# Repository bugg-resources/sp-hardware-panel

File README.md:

# sp-hardware-panel

This repository contains the KiCad source files for the panelled version of the PCBs required for the Bugg recording device (``main``, ``led``, and ``mic``). 

Also hosted here is the itemised BoM for the whole project.

For a full overview of the design of the Bugg recording device and practical assembly instructions please refer to the [Bugg hardware handover document](https://raw.githubusercontent.com/bugg-resources/bugg-handover/master/bugg-handover.pdf?token=GHSAT0AAAAAABSRG7B7T6BEZWMJQBPE7FNYYSNI6KQ).

## Electronics overview

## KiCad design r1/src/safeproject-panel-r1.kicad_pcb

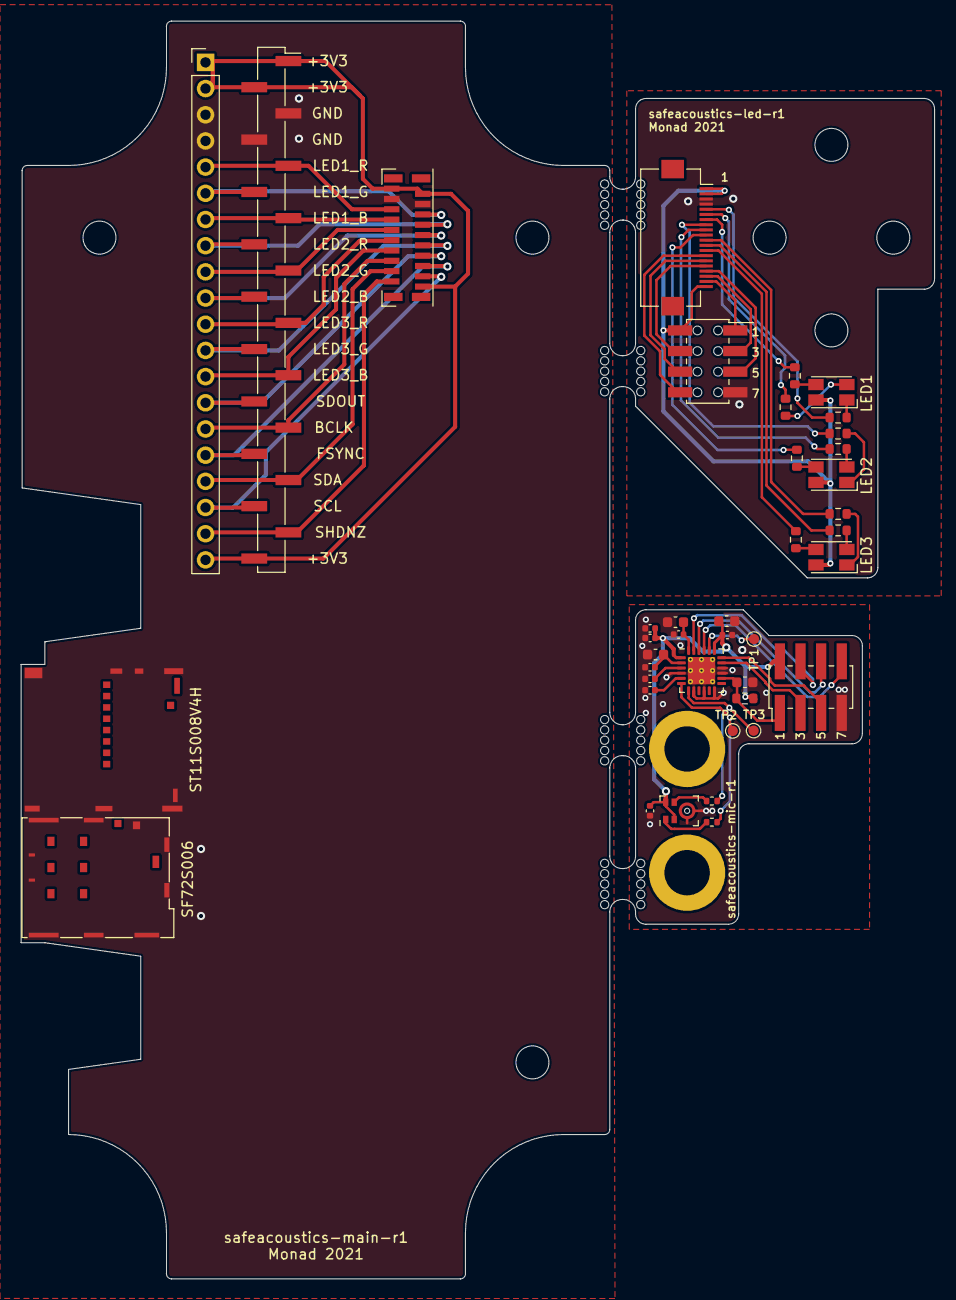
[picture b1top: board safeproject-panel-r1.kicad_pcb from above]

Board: 2 copper layers, 88.6 x 122.0 mm, 40 parts (0 on the bottom side), 37 nets.

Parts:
C1, C5, C7, C9, C11: 100nF; C_0402_1005Metric
C2, C3, C6: 1uF; C_0402_1005Metric
C4, C8, C10, C12: 10uF; C_0603_1608Metric
J1: 2842142-4; PinSocket_2x04_P2.00mm_Vertical_SMD_Bottom_or_Top_Entry_AMP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
J1#2: JAE_SIM_Card_SF72S006
J1#3: 2842142-4; PinHeader_2x04_P2.00mm_Vertical_SMD_AMPMODU
J2: Conn_01x20; Hirose_FH12-20S-0.5SH_1x20-1MP_P0.50mm_Horizontal
J2#2: Conn_01x20; Hirose_FH12-20S-0.5SVA_1x20-1MP_P0.50mm_Vertical
J3: Micro_SD_Card_Det_JAE_ST11; microSD_JAE_ST11S008V4H
J4: Conn_01x20; PinHeader_1x20_P2.54mm_Vertical_SMD_Pin1Right
J5: Conn_01x20; PinHeader_1x20_P2.54mm_Vertical
LED1, LED2, LED3: IN-P32TATRGB; LED_Avago_PLCC4_3.2x2.8mm_CW
MK1: SPH0641LU4H-1; Knowles_LGA-5_3.5x2.65mm
R1, R2#2, R3, R4, R5, R6: 22R; R_0603_1608Metric
R1#2, R2: 22R; R_0402_1005Metric
R3#2: 10k; R_0603_1608Metric
R7, R8, R9: 100R; R_0603_1608Metric
TP1, TP2, TP3: TestPoint; TestPoint_Pad_D1.0mm
U1: PCMD3180; QFN-24-1EP_4x4mm_P0.5mm_EP2.65x2.65mm_ThermalVias

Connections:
+3V3: C1.1, C6.2, C7.2, C10.1, C11.1, J1.2, J1#3.2, J2.1, J2.2, J2.20, LED1.2 (A), LED2.2 (A), LED3.2 (A), MK1.2 (SEL), MK1.5 (VDD), R3#2.2, U1.1 (AVDD), U1.19 (IOVDD)
/+3V3: J2#2.1, J2#2.2, J2#2.20, J4.1, J4.2, J4.20, J5.1, J5.2, J5.20
/BCLK: J1.6, J1#3.6, J2.15, J2#2.15, J4.15, J5.15, U1.22 (BCLK)
/FSYNC: J1.4, J1#3.4, J2.16, J2#2.16, J4.16, J5.16, U1.23 (FSYNC)
/GND: J1#2.SH, J2#2.3, J2#2.4, J3.GND, J4.3, J4.4, J5.3, J5.4
/LED1_B: J2.7, J2#2.7, J4.7, J5.7, R1.1
/LED1_G: J2.6, J2#2.6, J4.6, J5.6, R4.1
/LED1_R: J2.5, J2#2.5, J4.5, J5.5, R7.1
/LED2_B: J2.10, J2#2.10, J4.10, J5.10, R2#2.1
/LED2_G: J2.9, J2#2.9, J4.9, J5.9, R5.1
/LED2_R: J2.8, J2#2.8, J4.8, J5.8, R8.1
/LED3_B: J2.13, J2#2.13, J4.13, J5.13, R3.1
/LED3_G: J2.12, J2#2.12, J4.12, J5.12, R6.1
/LED3_R: J2.11, J2#2.11, J4.11, J5.11, R9.1
/SCL: J1.3, J1#3.3, J2.18, J2#2.18, J4.18, J5.18, U1.17 (SCL_MOSI)
/SDA: J1.5, J1#3.5, J2.17, J2#2.17, J4.17, J5.17, U1.18 (SDA_SSZ)
/SDOUT: J1.8, J1#3.8, J2.14, J2#2.14, J4.14, J5.14, U1.21 (SDOUT)
/SHDNZ: C12.2, J1.1, J1#3.1, J2.19, J2#2.19, J4.19, J5.19, R3#2.1, U1.14 (SHDNZ)
GND: C1.2, C2.1, C3.1, C4.1, C5.1, C6.1, C7.1, C8.1, C9.1, C10.2, C11.2, C12.1, J1.7, J1#3.7, J2.3, J2.4, MK1.3 (GND), U1.4 (AVSS), U1.8 (PDMDIN2_GPI2), U1.10 (PDMDIN3_GPI3), U1.12 (PDMDIN4_GPI4), U1.15 (ADDR1_MISO), U1.16 (ADDR0_SCLK), U1.25 (VSS_THERMAL)
unnamed: C2.2, U1.5 (MICBIAS)
unnamed: C3.2, U1.3 (VREF)
unnamed: C4.2, C5.2, U1.2 (AREG)
unnamed: C8.2, C9.2, U1.24 (DREG)
unnamed: LED1.1 (RK), R7.2
unnamed: LED1.3 (BK), R1.2
unnamed: LED1.4 (GK), R4.2
unnamed: LED2.1 (RK), R8.2
unnamed: LED2.3 (BK), R2#2.2
unnamed: LED2.4 (GK), R5.2
unnamed: LED3.1 (RK), R9.2
unnamed: LED3.3 (BK), R3.2
unnamed: LED3.4 (GK), R6.2
unnamed: MK1.1 (DATA), R1#2.1
unnamed: MK1.4 (CLOCK), R2.1
unnamed: R1#2.2, TP2.1, U1.6 (PDMDIN1_GPI1)
unnamed: R2.2, TP3.1, U1.7 (PDMCLK1_GPO1)
unnamed: TP1.1, U1.20 (GPIO1)

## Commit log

2021-01-25 Panel composed, mousebites in place
2021-01-25 DRC pass on panel
2021-04-01 Revision 2 panel
2021-04-01 Revised panel which should hopefully pass PCB train's DRC.
2021-04-02 Footprint table
2021-04-02 Tidy up board outline
2021-04-02 Fabrication data for r2 panel
2021-04-02 Fabrication data archive as issued to PCB Train
2021-04-02 r1 fabrication data
2021-04-02 r1 stencil data as issued to PCB Train
2021-04-02 r1 fabrication data as issued to Screenbond
2021-04-02 r1 panellisation by Screenbond
2021-04-02 Interactive HTML bom created wtih the fancy Interactive Bom plugin
2021-04-03 Add 100 to mic designators and 200 to LED designators to prevent collisions and bring panel into parity with the individual sub-boards
2021-04-03 Set names of mounting holes and threaded spacers, and include them into the BoM appropriately. Exclude mousebites from BoM
2021-04-03 Exclude mousebites from Bom, attempt 2
2021-04-03 Correct value for LED FFC
2021-05-20 Tweak some resistor values. Unsure which!
2021-05-20 Remove redundant cad data archive
2021-05-20 Complete build data zip
2021-05-20 Preliminary placement data for RFQ
2021-05-23 r2 version of the panel
2021-05-23 r3 production panel
2021-05-23 Add jeffmakes-kicad-library as submodule
2021-05-24 There were some vias inside pads. Moved away
2021-05-24 Panel released for production
2021-05-26 Import BOM from r2, update with r3 changes. Checked all stock in hand, updated the Rcvd. Prod coloumn to reflect stock levels. Used data to order more stuff from Mouser
2021-05-26 Add coin cells, FFC's
2021-05-27 Update LED resistor values to make them less blinding
2021-05-27 CSV BOM export
2021-05-27 Update BOM to include more mechanical parts
2021-05-27 Update BOM with correct LED resistor values
2021-05-27 Hide values in Fab layer so we can export it with RefDes's only.
2021-05-28 Add pin 1 marker to modem on F.Fab
2021-05-28 BOM update - check in some more parts
2021-05-28 gitignore Libreoffice lock files
2021-05-28 Interactive BoM
2021-05-28 Panellised production data from Screenbond
2021-05-28 Gerbers released for production
2021-05-28 Remove intermediate CSV bom data so as not to confuse anyone
2021-05-28 Move production panel data into the fabrication folder
2021-05-28 Placement data and readme
2021-05-28 Add assembly data to build archive
2021-07-25 Add a few more details to BoM
2022-04-07 Create LICENSE

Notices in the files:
README.md:
cc-by-nc-sa-shield
